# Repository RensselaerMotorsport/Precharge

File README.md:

# Precharge
Repo For RM's Precharge Board Design

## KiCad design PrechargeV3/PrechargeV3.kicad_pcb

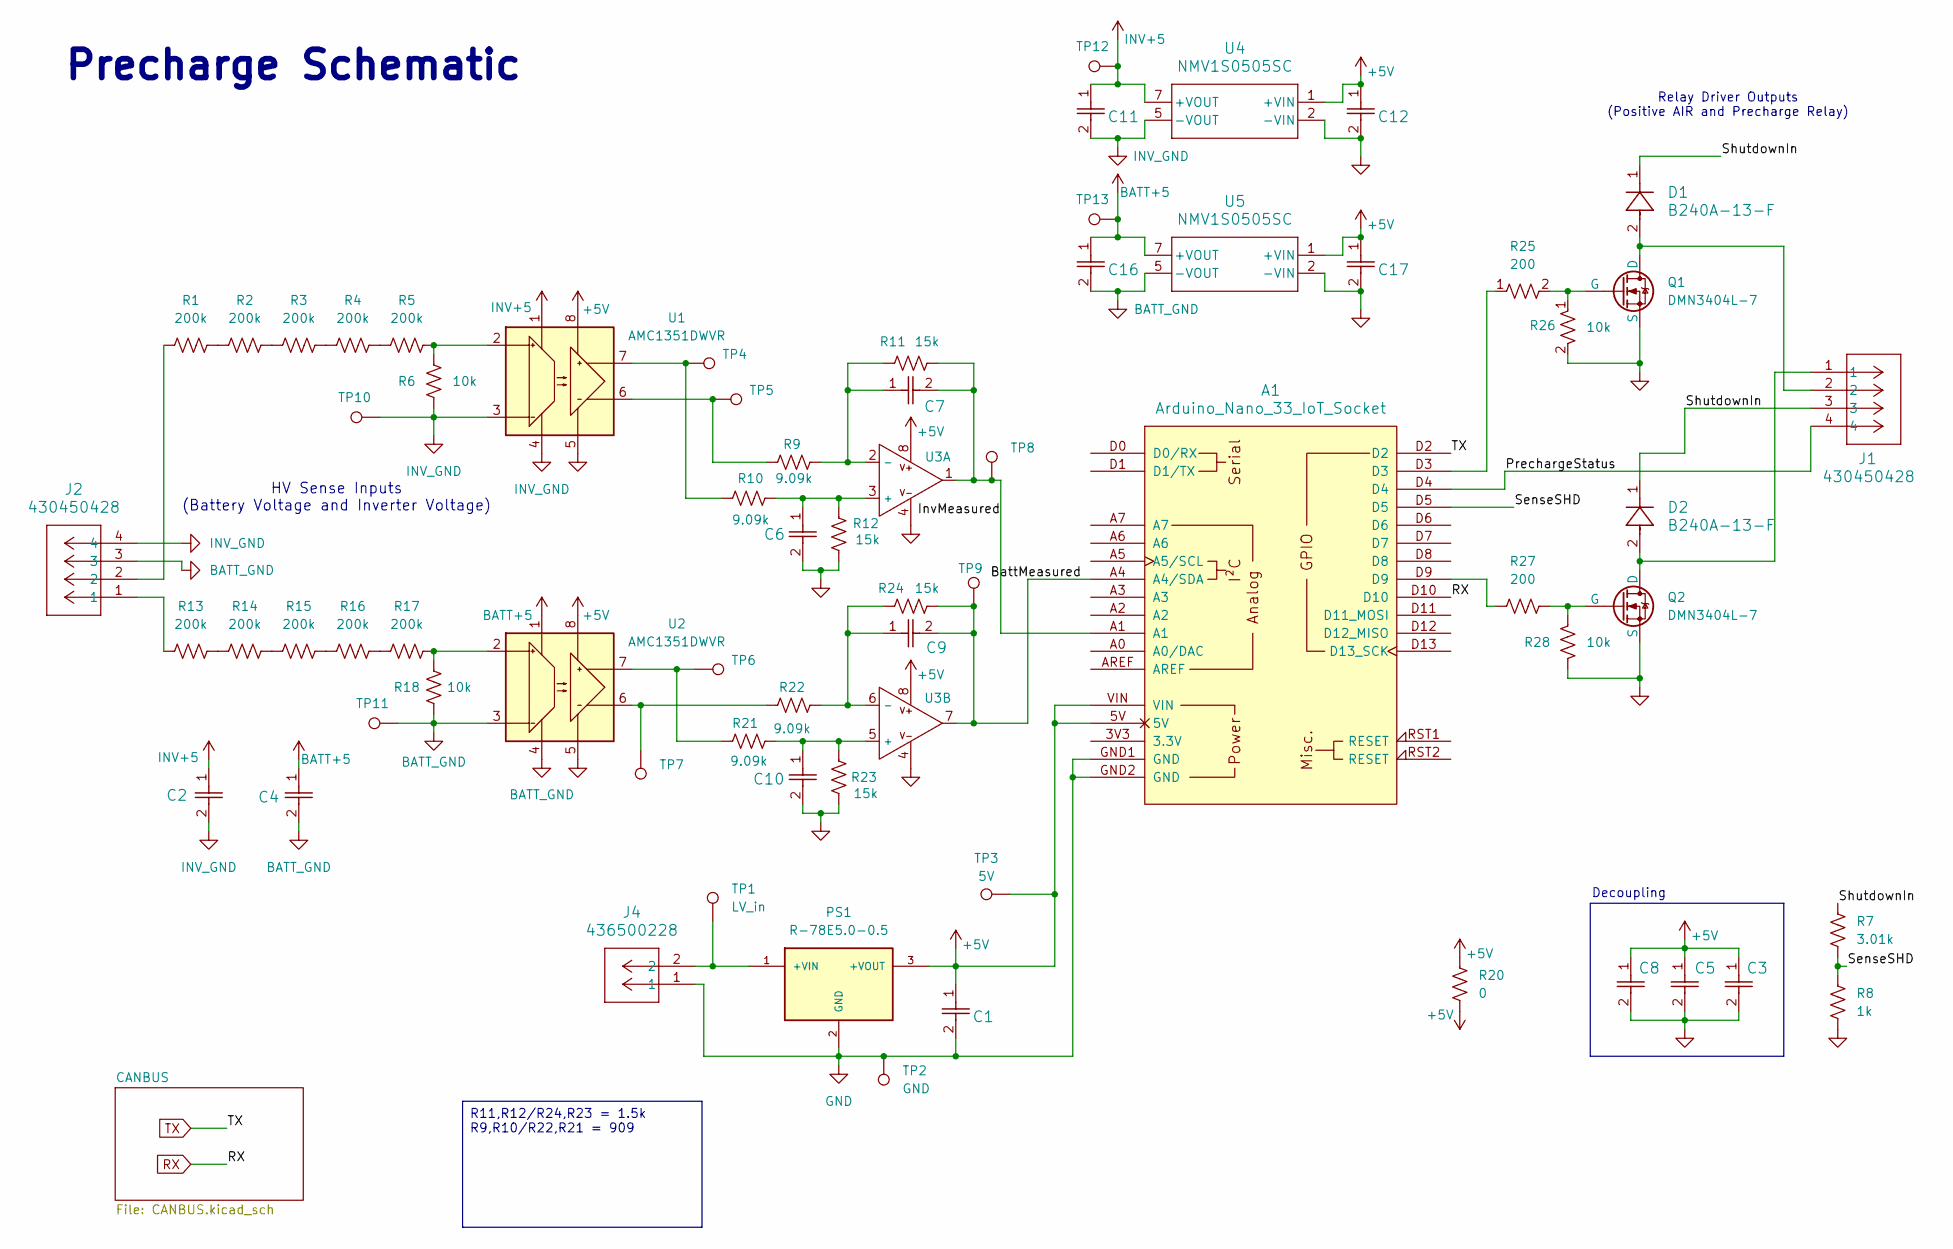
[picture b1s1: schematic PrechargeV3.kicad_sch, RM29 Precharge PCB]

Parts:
A1: Arduino_Nano_33_IoT_Socket
C1, C11, C12, C16, C17: 10u; C_1210_3225Metric
C2, C3, C4, C5, C8: 1u; C_0805_2012Metric
C6, C7, C9, C10: 330p; C_0603_1608Metric
D1, D2: B240A-13-F; SMA_DIO
J1, J2: 430450428; CONN_SD-43045-010_04_MOL
J4: 436500228; CONN_SD-43650-010_02_MOL
PS1: R-78E5.0-0.5; PARTREV 4
Q1, Q2: DMN3404L-7; SOT23_DIO
R1, R2, R3, R4, R5, R13, R14, R15, R16, R17: 200k; C_0805_2012Metric
R6, R18: 10k; C_0805_2012Metric
R7: 3.01k; R_0603_1608Metric
R8: 1k; R_0603_1608Metric
R9, R10, R21, R22: 9.09k; R_0603_1608Metric
R11, R12, R23, R24: 15k; R_0603_1608Metric
R20: 0; R_0805_2012Metric
R25, R27: 200; R_0603_1608Metric
R26, R28: 10k; R_0603_1608Metric
TP1: LV_in; TestPoint_Pad_D1.0mm
TP2: GND; TestPoint_Pad_D1.0mm
TP3: 5V; TestPoint_Pad_D1.0mm
TP4: Vinv_LV+; TestPoint_Pad_D1.0mm
TP5: Vinv_LV-; TestPoint_Pad_D1.0mm
TP6: Vbatt_LV+; TestPoint_Pad_D1.0mm
TP7: Vbatt_LV-; TestPoint_Pad_D1.0mm
TP8: Inv_measured; TestPoint_Pad_D1.0mm
TP9: Batt_Measured; TestPoint_Pad_D1.0mm
TP10: INV_GND; TestPoint_Pad_D1.0mm
TP11: BATT_GND; TestPoint_Pad_D1.0mm
TP12: INV_+5; TestPoint_Pad_D1.0mm
TP13: BATT_+5; TestPoint_Pad_D1.0mm
U1, U2: AMC1351DWVR; SOIC8_DWV_TEX
U3: TLV9002QDKRQ1; VSSOP8_DGK_TEX
U4, U5: NMV1S0505SC; SIP4_NMV1S0_MUR

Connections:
+5V: A1.5V, A1.VIN, C1.1, C3.1, C5.1, C8.1, C12.1, C17.1, PS1.3 (+VOUT), R20.1, R20.2, TP3.1, U1.8 (VDD2), U2.8 (VDD2), U3.8, U4.1 (+VIN), U5.1 (+VIN)
/BattMeasured: A1.A4 (A4/SDA), C9.2, R24.1, TP9.1, U3.7
/InvMeasured: A1.A1, C7.2, R11.1, TP8.1, U3.1
/PrechargeStatus: A1.D4, J1.4
/SenseSHD: A1.D5, R7.1, R8.2
/ShutdownIn: D1.1, D2.1, J1.3, R7.2
BATT+5: C4.1, C16.1, TP13.1, U2.1 (VDD1), U5.7 (+VOUT)
BATT_GND: C4.2, C16.2, J2.3, R18.1, TP11.1, U2.3 (VINN), U2.4 (GND1), U5.5 (-VOUT)
GND: A1.GND1 (GND), A1.GND2 (GND), C1.2, C3.2, C5.2, C6.2, C8.2, C10.2, C12.2, C17.2, J4.1, PS1.2 (GND), Q1.2 (S), Q2.2 (S), R8.1, R12.1, R23.1, R26.2, R28.2, TP2.1, U1.5 (GND2), U2.5 (GND2), U3.4, U4.2 (-VIN), U5.2 (-VIN); also elsewhere on the board
INV+5: C2.1, C11.1, TP12.1, U1.1 (VDD1), U4.7 (+VOUT)
INV_GND: C2.2, C11.2, J2.4, R6.1, TP10.1, U1.3 (VINN), U1.4 (GND1), U4.5 (-VOUT)
unnamed: A1.D3, R25.1
unnamed: A1.D9, R27.1
unnamed: J2.1, R13.1
unnamed: J2.2, R1.1
unnamed: J4.2, PS1.1 (+VIN), TP1.1
unnamed: D1.2, J1.2, Q1.3 (D)
unnamed: Q1.1 (G), R25.2, R26.1
unnamed: D2.2, J1.1, Q2.3 (D)
unnamed: Q2.1 (G), R27.2, R28.1
unnamed: R1.2, R2.1
unnamed: R2.2, R3.1
unnamed: R3.2, R4.1
unnamed: R4.2, R5.1
unnamed: R13.2, R14.1
unnamed: R14.2, R15.1
unnamed: R15.2, R16.1
unnamed: R16.2, R17.1
unnamed: R5.2, R6.2, U1.2 (VINP)
unnamed: R9.1, TP5.1, U1.6 (VOUTN)
unnamed: R10.1, TP4.1, U1.7 (VOUTP)
unnamed: R17.2, R18.2, U2.2 (VINP)
unnamed: R22.1, TP7.1, U2.6 (VOUTN)
unnamed: R21.1, TP6.1, U2.7 (VOUTP)
unnamed: C6.1, R10.2, R12.2, U3.3 (+)
unnamed: C7.1, R9.2, R11.2, U3.2 (-)
unnamed: C10.1, R21.2, R23.2, U3.5 (+)
unnamed: C9.1, R22.2, R24.2, U3.6 (-)
RX: A1.D10; also elsewhere on the board
TX: A1.D2; also elsewhere on the board

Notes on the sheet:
Precharge Schematic
HV Sense Inputs (Battery Voltage and Inverter Voltage)
Decoupling
Relay Driver Outputs (Positive AIR and Precharge Relay)
R11,R12/R24,R23 = 1.5k R9,R10/R22,R21 = 909

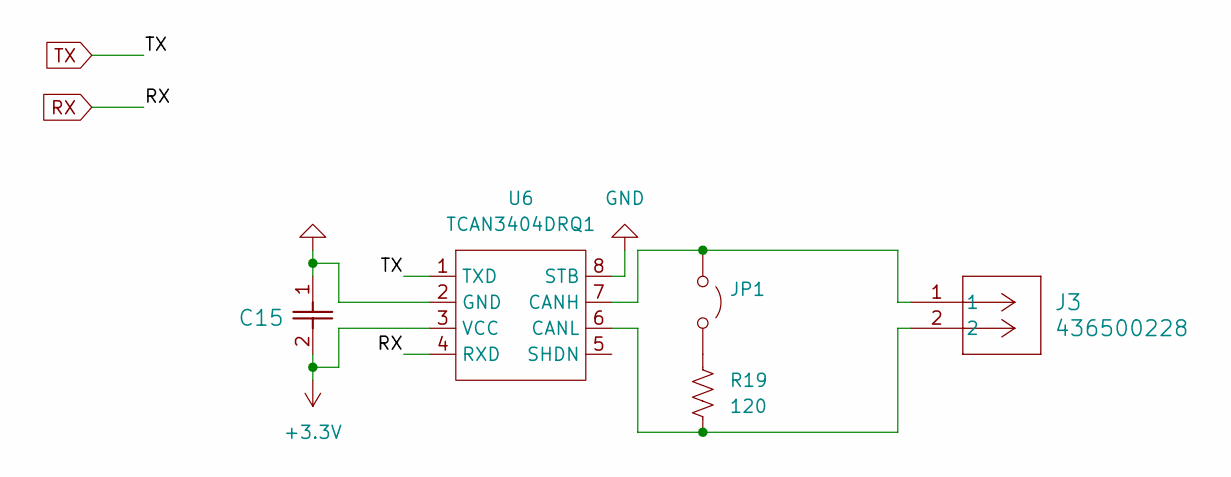
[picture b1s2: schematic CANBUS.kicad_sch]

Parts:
C15: 1u; C_0805_2012Metric
J3: 436500228; CONN_SD-43650-010_02_MOL
JP1: Jumper_2_Open; PinHeader_1x02_P2.54mm_Vertical
R19: 120; R_0603_1608Metric
U6: TCAN3404DRQ1; SOIC8_D_TEX

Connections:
+3.3V: C15.2, U6.3 (VCC)
GND: C15.1, U6.2 (GND), U6.8 (STB); also elsewhere on the board
unnamed: J3.1, JP1.1 (A), U6.7 (CANH)
unnamed: JP1.2 (B), R19.1
unnamed: J3.2, R19.2, U6.6 (CANL)
RX: U6.4 (RXD); also elsewhere on the board
TX: U6.1 (TXD); also elsewhere on the board

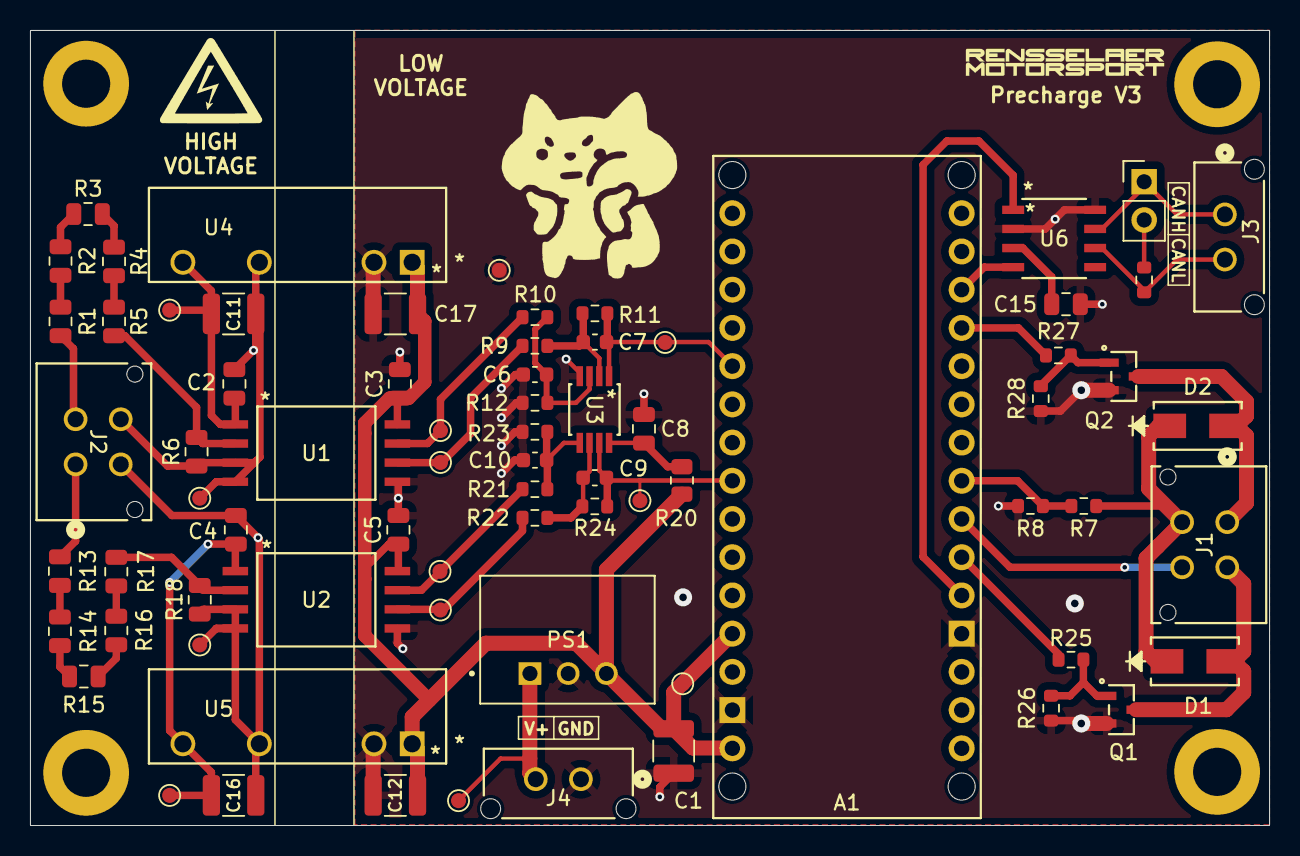
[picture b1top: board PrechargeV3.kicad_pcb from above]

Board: 2 copper layers, 82.4 x 52.8 mm, 73 parts (0 on the bottom side), 44 nets.

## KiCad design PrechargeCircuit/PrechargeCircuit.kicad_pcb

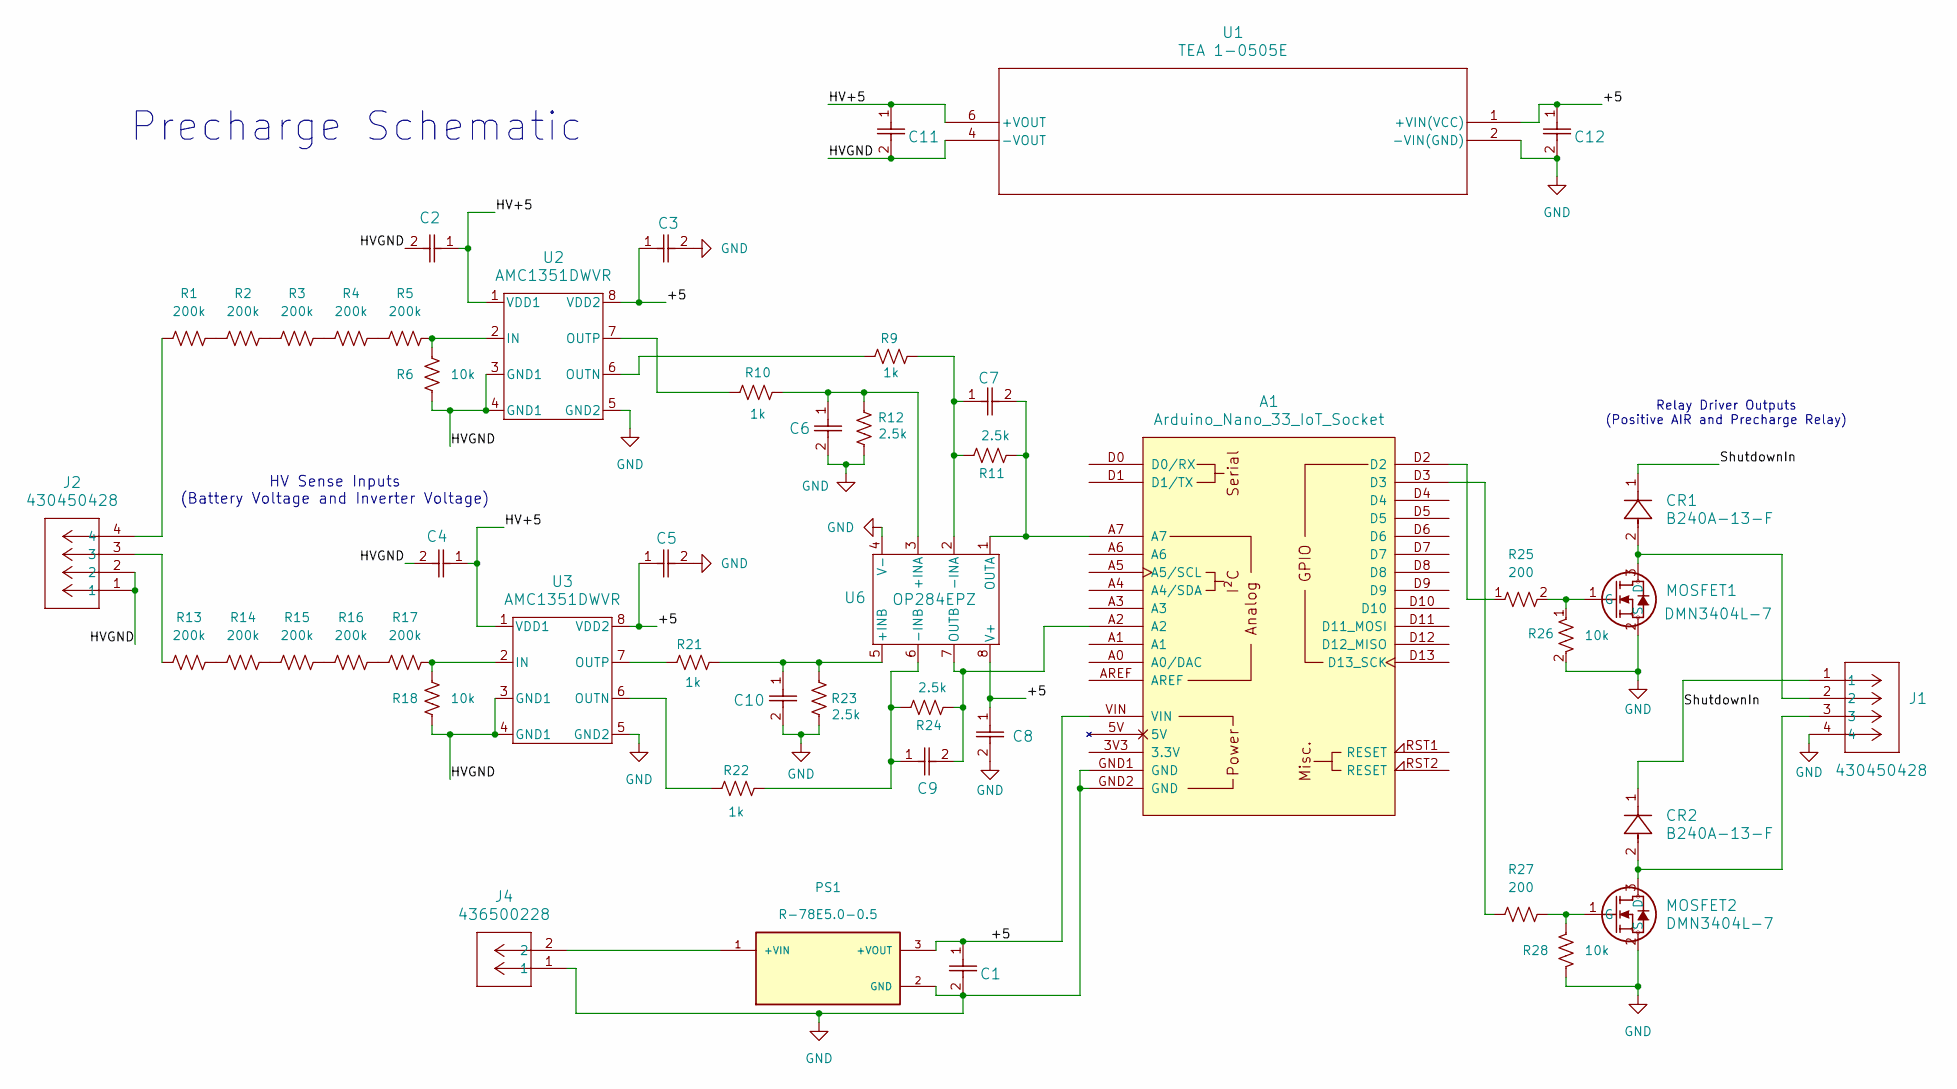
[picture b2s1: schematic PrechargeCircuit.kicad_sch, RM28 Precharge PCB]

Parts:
A1: Arduino_Nano_33_IoT_Socket
C1, C11, C12: C324C106K3R5TA; CAP_C324C_MR_X7R_KEM
C2, C3, C4, C5, C8: K104K10X7RF5UH5; K104K10X7RF5UH5_VIS
C6, C7, C9, C10: K331K15X7RF5TL2; CAP_K-SERIES_15-L2_VIS
CR1, CR2: B240A-13-F; SMA_DIO-L
J1, J2: 430450428; CONN_SD-43045-010_04_MOL
J4: 436500228; CONN_SD-43650-010_02_MOL
MOSFET1, MOSFET2: DMN3404L-7; SOT23_DIO-L
PS1: R-78E5.0-0.5; CONV_R-78E5.0-0.5; PARTREV 4
R1, R2, R3, R4, R5, R13, R14, R15, R16, R17: 200k; R_Axial_DIN0207_L6.3mm_D2.5mm_P10.16mm_Horizontal
R6, R18, R26, R28: 10k; R_Axial_DIN0207_L6.3mm_D2.5mm_P10.16mm_Horizontal
R9, R10, R21, R22: 1k; R_Axial_DIN0207_L6.3mm_D2.5mm_P10.16mm_Horizontal
R11, R12, R23, R24: 2.5k; R_Axial_DIN0207_L6.3mm_D2.5mm_P10.16mm_Horizontal
R25, R27: 200; R_Axial_DIN0207_L6.3mm_D2.5mm_P10.16mm_Horizontal
U1: TEA 1-0505E; TEA 1E_TRP
U2, U3: AMC1351DWVR; SOIC8_DWV_TEX
U6: OP284EPZ; N_8_ADI

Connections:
/+5: A1.VIN, C1.1, C3.1, C5.1, C8.1, C12.1, PS1.3 (+VOUT), U1.1 (+VIN(VCC)), U2.8 (VDD2), U3.8 (VDD2), U6.8 (V+)
/HV+5: C2.1, C4.1, C11.1, U1.6 (+VOUT), U2.1 (VDD1), U3.1 (VDD1)
/SenseSHD: A1.D4; also elsewhere on the board
/ShutdownIn: CR1.1, CR2.1, J1.1; also elsewhere on the board
GND: A1.GND1 (GND), A1.GND2 (GND), C1.2, C3.2, C5.2, C6.2, C8.2, C10.2, C12.2, J1.4, J4.1, MOSFET1.2 (S), MOSFET2.2 (S), PS1.2 (GND), R12.1, R23.1, R26.2, R28.2, U1.2 (-VIN(GND)), U2.5 (GND2), U3.5 (GND2), U6.4 (V-); also elsewhere on the board
unnamed: A1.D2, R25.1
unnamed: A1.D3, R27.1
unnamed: J2.3, R13.1
unnamed: J2.4, R1.1
unnamed: CR1.2, J1.2, MOSFET1.3 (D)
unnamed: MOSFET1.1 (G), R25.2, R26.1
unnamed: CR2.2, J1.3, MOSFET2.3 (D)
unnamed: MOSFET2.1 (G), R27.2, R28.1
unnamed: J4.2, PS1.1 (+VIN)
unnamed: R1.2, R2.1
unnamed: R2.2, R3.1
unnamed: R3.2, R4.1
unnamed: R4.2, R5.1
unnamed: R13.2, R14.1
unnamed: R14.2, R15.1
unnamed: R15.2, R16.1
unnamed: R16.2, R17.1
unnamed: R5.2, R6.2, U2.2 (IN)
unnamed: R9.1, U2.6 (OUTN)
unnamed: R10.1, U2.7 (OUTP)
unnamed: R17.2, R18.2, U3.2 (IN)
unnamed: R22.1, U3.6 (OUTN)
unnamed: R21.1, U3.7 (OUTP)
unnamed: C6.1, R10.2, R12.2, U6.3 (+INA)
unnamed: C10.1, R21.2, R23.2, U6.5 (+INB)
unnamed: C7.1, R9.2, R11.2, U6.2 (-INA)
unnamed: C9.1, R22.2, R24.2, U6.6 (-INB)
unnamed: A1.A7, C7.2, R11.1, U6.1 (OUTA)
unnamed: A1.A2, C9.2, R24.1, U6.7 (OUTB)

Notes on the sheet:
Precharge Schematic
HV Sense Inputs (Battery Voltage and Inverter Voltage)
Relay Driver Outputs (Positive AIR and Precharge Relay)

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
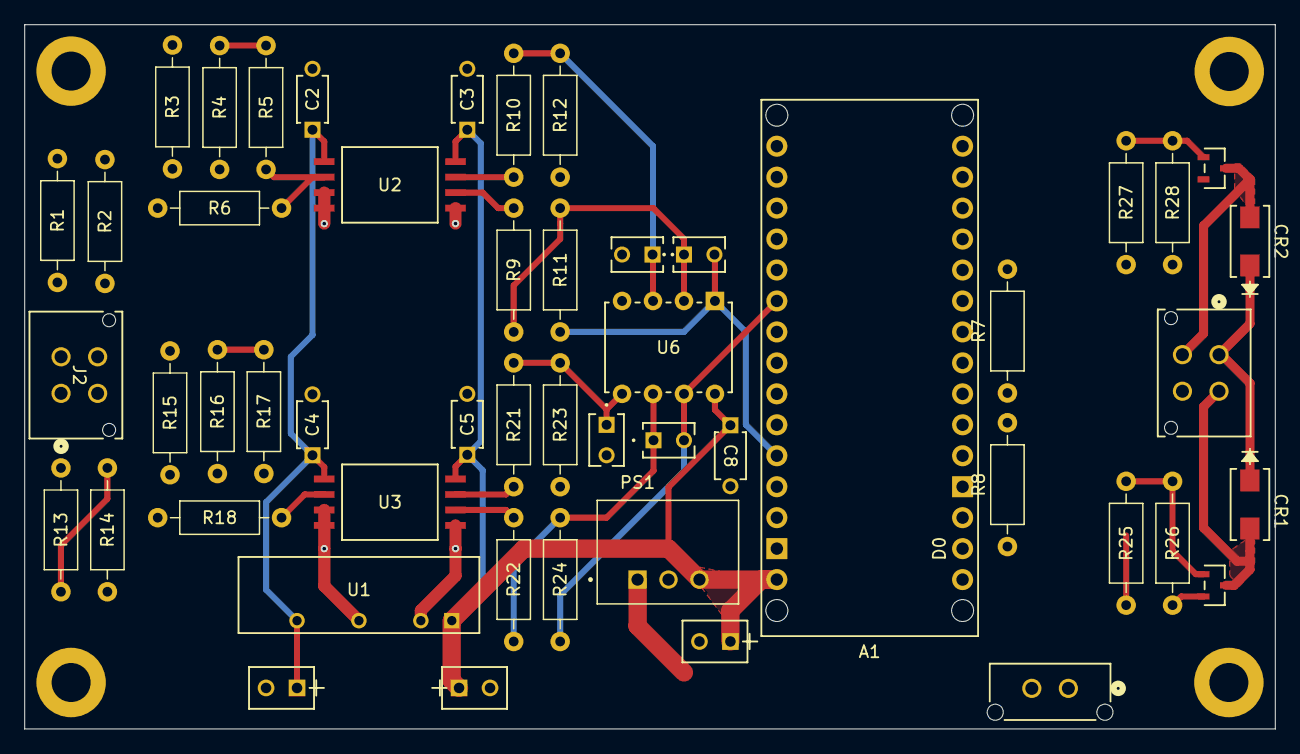
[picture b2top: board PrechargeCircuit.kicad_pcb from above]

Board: 2 copper layers, 102.6 x 57.8 mm, 51 parts (0 on the bottom side), 35 nets.

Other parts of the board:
R7, R8: R_US; R_Axial_DIN0207_L6.3mm_D2.5mm_P10.16mm_Horizontal

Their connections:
/SenseSHD: R7.1, R8.2; also elsewhere on the board
/ShutdownIn: R7.2; also elsewhere on the board
GND: R8.1; also elsewhere on the board

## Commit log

2025-05-07 Precharge V1
2026-03-18 Updated Schematic For ESF
2026-03-22 Started Precharge V3
2026-03-27 Started Layout
2026-03-31 Finished Layout
2026-04-02 Updated Layout
2026-05-26 Precharge V3.0 STM32 code
    Precharge control software for version 3.0 of the precharge board using an stm32f0 nucleo board.
2026-05-30 Precharge state machine & 3.3v component adjustments
    Precharge state machine written for stm32. Differential op-amp and shutdown sense resistor values changed from 5v logic level mcu to 3.3v one.
